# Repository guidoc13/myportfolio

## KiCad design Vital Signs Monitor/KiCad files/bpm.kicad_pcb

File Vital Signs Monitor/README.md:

# Data Logger de Signos Vitales (LPC845 + ESP32)

## Descripción General
Este proyecto consiste en el desarrollo de un sistema embebido para la adquisición, registro y monitoreo de señales biomédicas. El sistema utiliza un microcontrolador **ARM Cortex-M0+ (LPC845)** para el procesamiento de señales y un módulo **ESP** para la transmisión de datos, integrando lógicas de 3.3V y protecciones de hardware.

## Especificaciones Técnicas y Criterios de Diseño
Para garantizar la integridad de las señales analógicas y la estabilidad del sistema, se aplicaron los siguientes criterios durante el diseño en **KiCad**:

* **Integridad de Señal:** Implementación de capacitores de desacople de 100nF en los pines de alimentación de cada dispositivo para filtrar ruido de alta frecuencia.
* **Gestión de Retornos:** Diseño de un plano de masa (*GND Pour*) continuo en la capa superior (*Top Layer*) para blindaje electromagnético y minimización de corrientes de retorno.
* **Compatibilidad de Lógica:** Manejo de niveles lógicos de 3.3V y diseño de protecciones de hardware para preservar la integridad de los microcontroladores.

## Documentación y Fabricación
* **Paquete Gerber:** Generación de archivos vectoriales para la fabricación de la placa (Cobre, Máscara y Serigrafía).
* **Bill of Materials (BOM):** Lista de materiales detalladas para los componentes.
* **Composición 3D:** Modelado y visualización final de la placa mediante archivos .step.

## Vistas del Proyecto

## Ruteo de Capas (Top & Bottom)

---

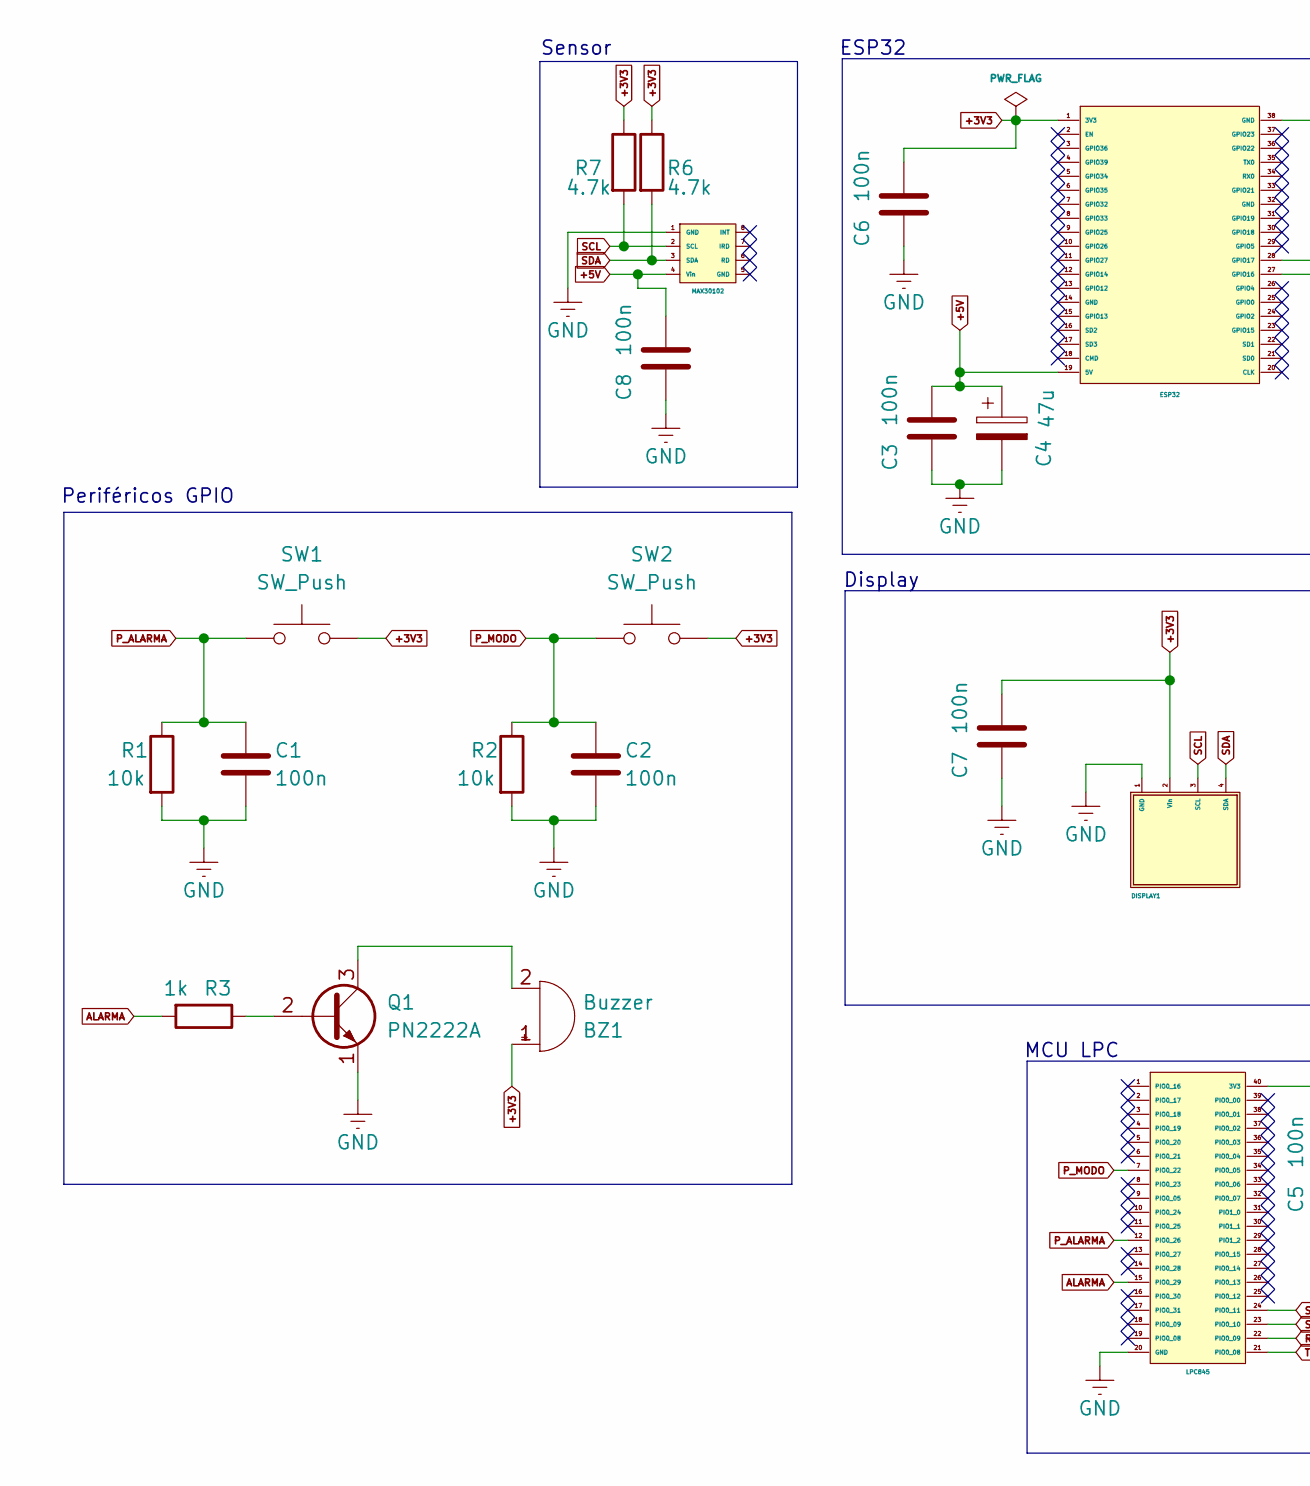
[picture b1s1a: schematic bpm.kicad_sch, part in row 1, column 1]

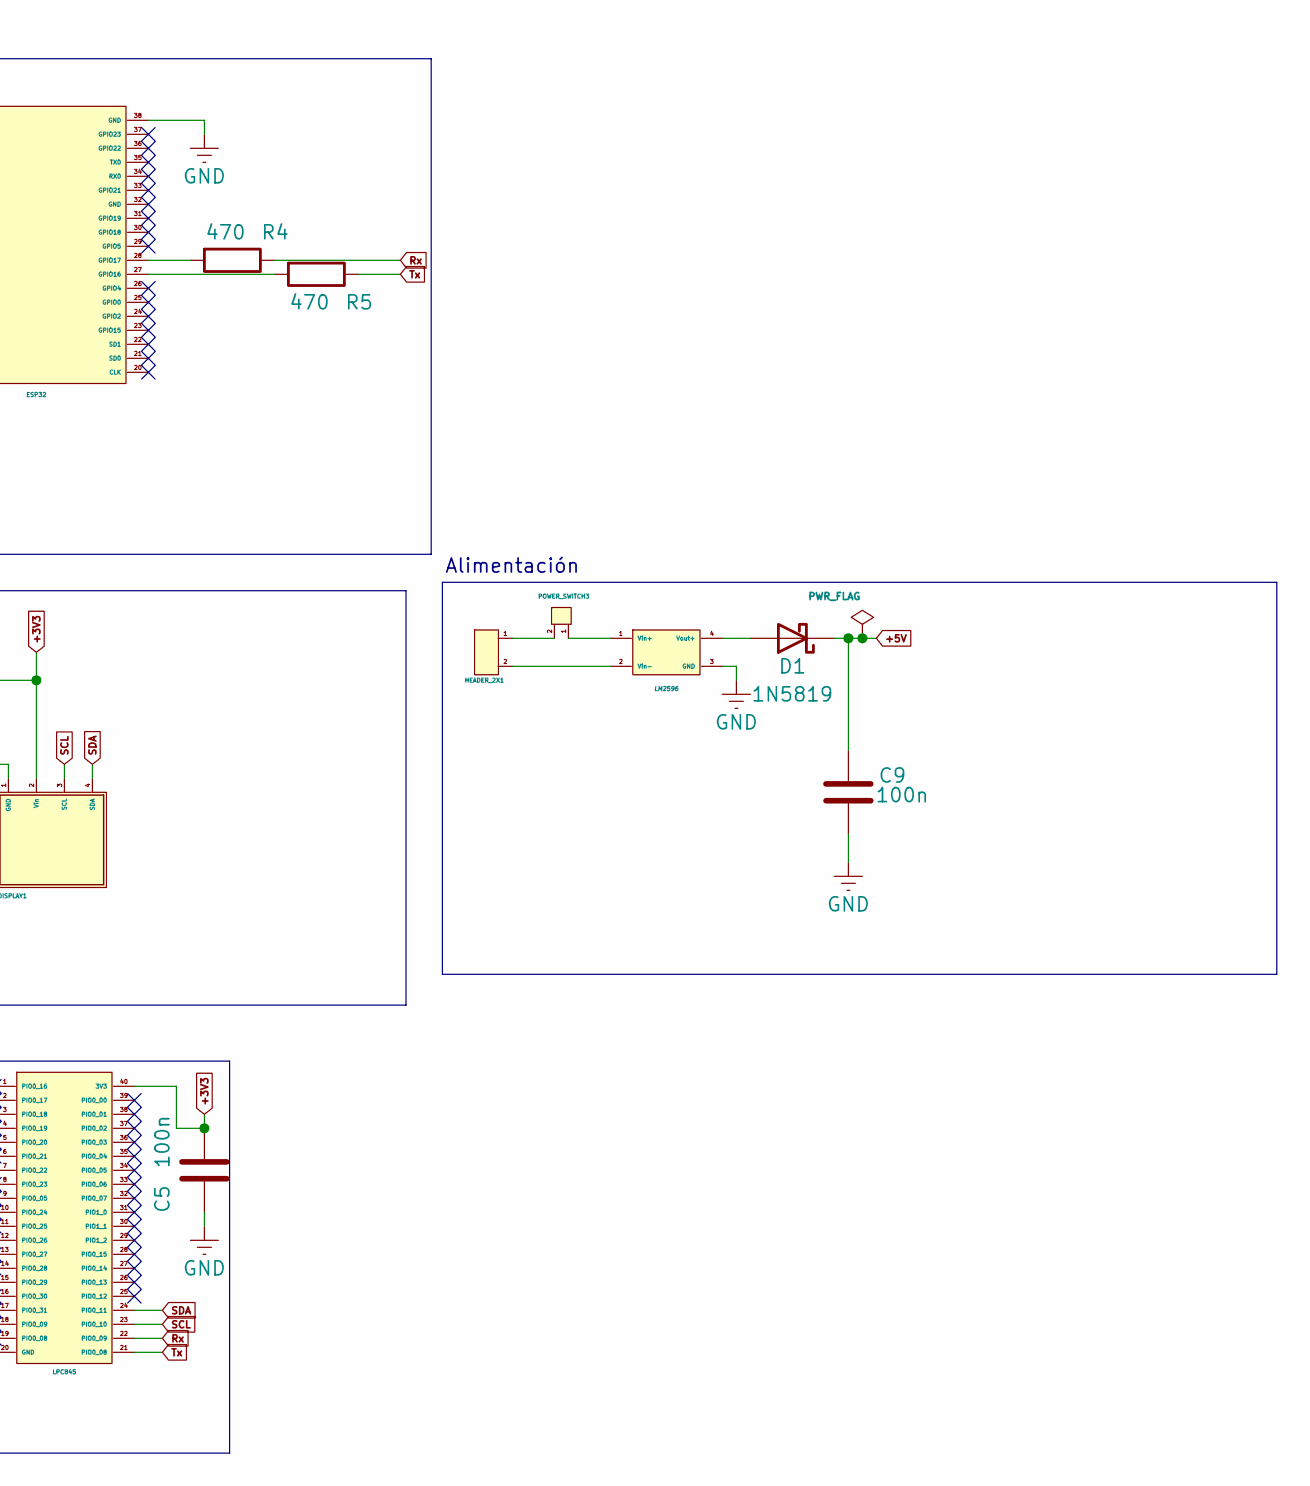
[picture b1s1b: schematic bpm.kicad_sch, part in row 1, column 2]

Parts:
BZ1: Buzzer; Buzzer_12x9.5RM7.6
C1, C2, C3, C5, C6, C7, C8, C9: 100n; C_Disc_D4.3mm_W1.9mm_P5.00mm
C4: 47u; CP_Radial_D5.0mm_P2.50mm
D1: 1N5819; D_DO-41_SOD81_P10.16mm_Horizontal
DISPLAY1: DISPLAY_128X64
ESP32: ESP32_MODULE
HEADER_2X1: TerminalBlock_MaiXu_MX126-5.0-02P_1x02_P5.00mm
LM2596: LM2596_MODULE
LPC845: LPC845_MODULE
MAX30102: MAX30102
POWER_SWITCH3: SW_CK_JS202011CQN_DPDT_Straight
Q1: PN2222A; TO-92_Inline
R1, R2: 10k; R_Axial_DIN0207_L6.3mm_D2.5mm_P10.16mm_Horizontal
R3: 1k; R_Axial_DIN0207_L6.3mm_D2.5mm_P10.16mm_Horizontal
R4, R5: 470; R_Axial_DIN0207_L6.3mm_D2.5mm_P10.16mm_Horizontal
R6, R7: 4.7k; R_Axial_DIN0207_L6.3mm_D2.5mm_P10.16mm_Horizontal
SW1, SW2: SW_Push; SW_PUSH_6mm

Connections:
+3V3: BZ1.1 (+), C5.2, C6.2, C7.2, DISPLAY1.2 (Vin), ESP32.1 (3V3), LPC845.40 (3V3), R6.1, R7.1, SW1.2, SW2.2
+5V: C3.2, C4.1, C8.2, C9.2, D1.1 (K), ESP32.19 (5V), MAX30102.4 (Vin)
ALARMA: LPC845.15 (PIO0_29), R3.2
GND: C1.2, C2.2, C3.1, C4.2, C5.1, C6.1, C7.1, C8.1, C9.1, DISPLAY1.1 (GND), ESP32.38 (GND), LM2596.3 (GND), LPC845.20 (GND), MAX30102.1 (GND), Q1.1 (E), R1.2, R2.2
unnamed: BZ1.2 (-), Q1.3 (C)
unnamed: D1.2 (A), LM2596.4 (Vout+)
unnamed: ESP32.27 (GPIO16), R5.2
unnamed: ESP32.28 (GPIO17), R4.2
unnamed: HEADER_2X1.1, POWER_SWITCH3.2
unnamed: LM2596.1 (Vin+), POWER_SWITCH3.1
unnamed: HEADER_2X1.2, LM2596.2 (Vin-)
unnamed: Q1.2 (B), R3.1
P_ALARMA: C1.1, LPC845.12 (PIO0_26), R1.1, SW1.1
P_MODO: C2.1, LPC845.7 (PIO0_22), R2.1, SW2.1
Rx: LPC845.22 (PIO0_09), R4.1
SCL: DISPLAY1.3 (SCL), LPC845.23 (PIO0_10), MAX30102.2 (SCL), R7.2
SDA: DISPLAY1.4 (SDA), LPC845.24 (PIO0_11), MAX30102.3 (SDA), R6.2
Tx: LPC845.21 (PIO0_08), R5.1

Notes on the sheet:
ESP32
Display
MCU LPC
Alimentación
Sensor
Periféricos GPIO

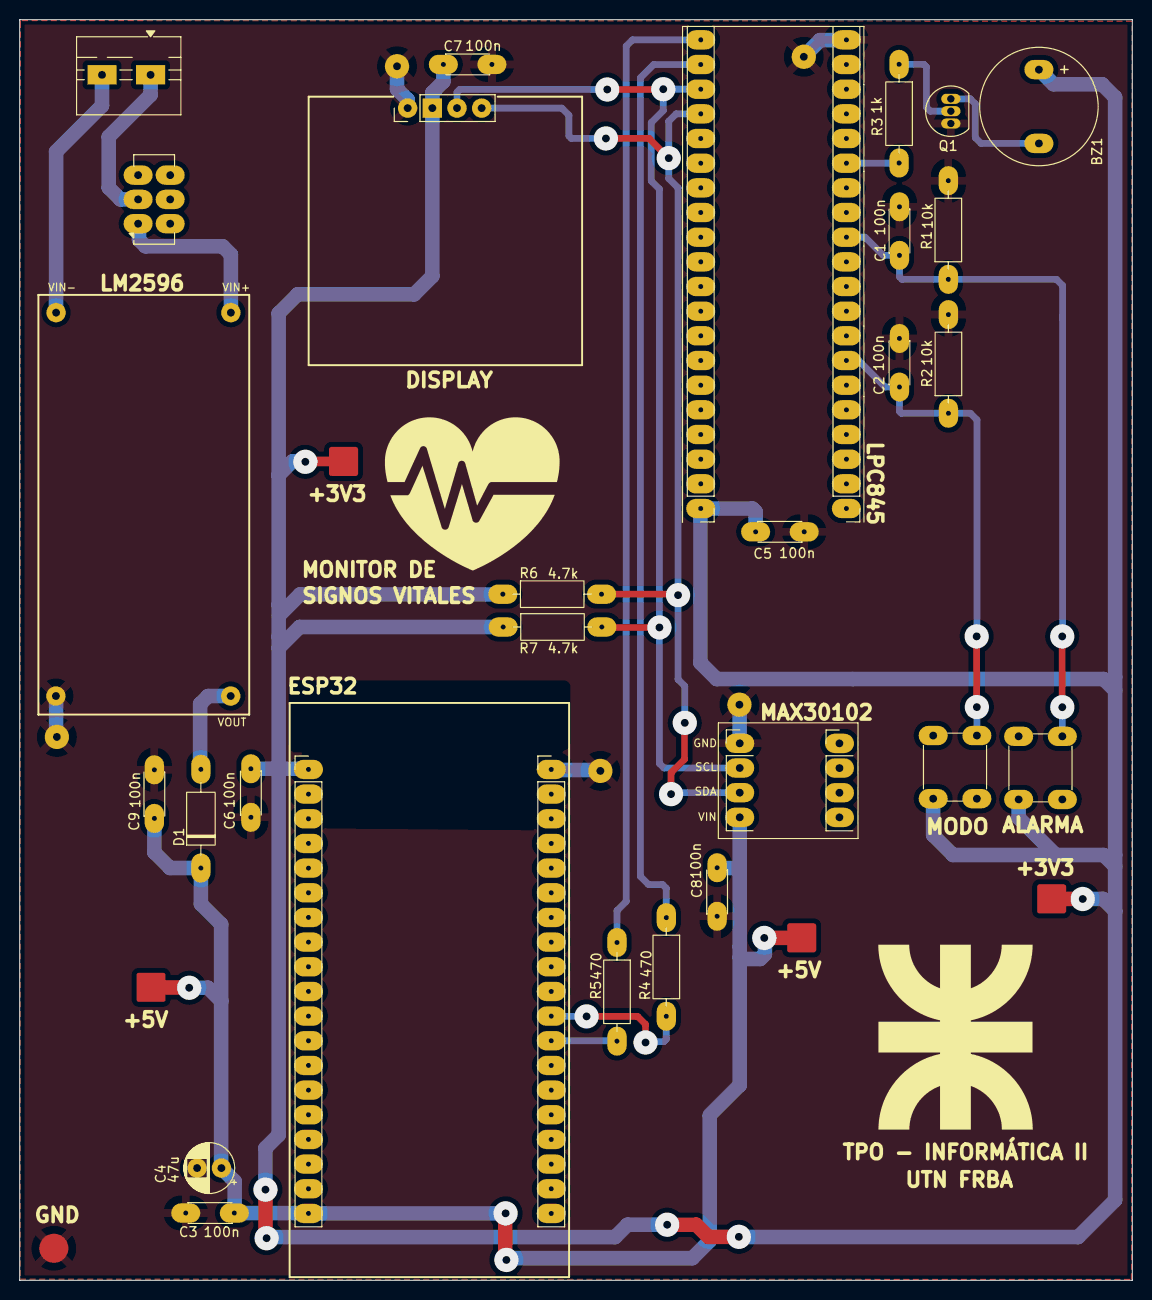
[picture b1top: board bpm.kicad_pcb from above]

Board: 2 copper layers, 114.6 x 129.8 mm, 28 parts (0 on the bottom side), 18 nets.

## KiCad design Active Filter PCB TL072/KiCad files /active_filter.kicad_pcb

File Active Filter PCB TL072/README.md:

# Diseño de PCB: Filtro Analógico Activo (Low Pass & Notch) con TL072
Este proyecto consiste en el diseño y ruteo de una PCB para un Filtro Analógico Activo del tipo Pasa Bajos y Notch utilizando el Amplificador Operacional TL072. El objetivo principal fue realizar el análisis de respuesta en frecuencia empleando un Analizador de Redes.    

## Vistas del Proyecto

## Criterios de Diseño Aplicados

Durante el ruteo de la placa, los criterios de diseño que se tomaron para garantizar la estabilidad del circuito fueron:

* **Desacople de Alimentación Vcc:** Ubicación de capacitores cerámicos de 100nF en los pines de +Vcc y -Vcc para mitigar los efectos del ruido de alta frecuencia en la entrada de la alimentación del Op. Amp.
* **Plano GND en la Top Layer:** Implementación de un plano de masa continuo (*GND Pour*) en la capa Top para blindar el circuito y reducir significativamente las corrientes de retorno.

## Ruteo de Capas (Top & Bottom)

## Respuesta en frecuencia de cada filtro

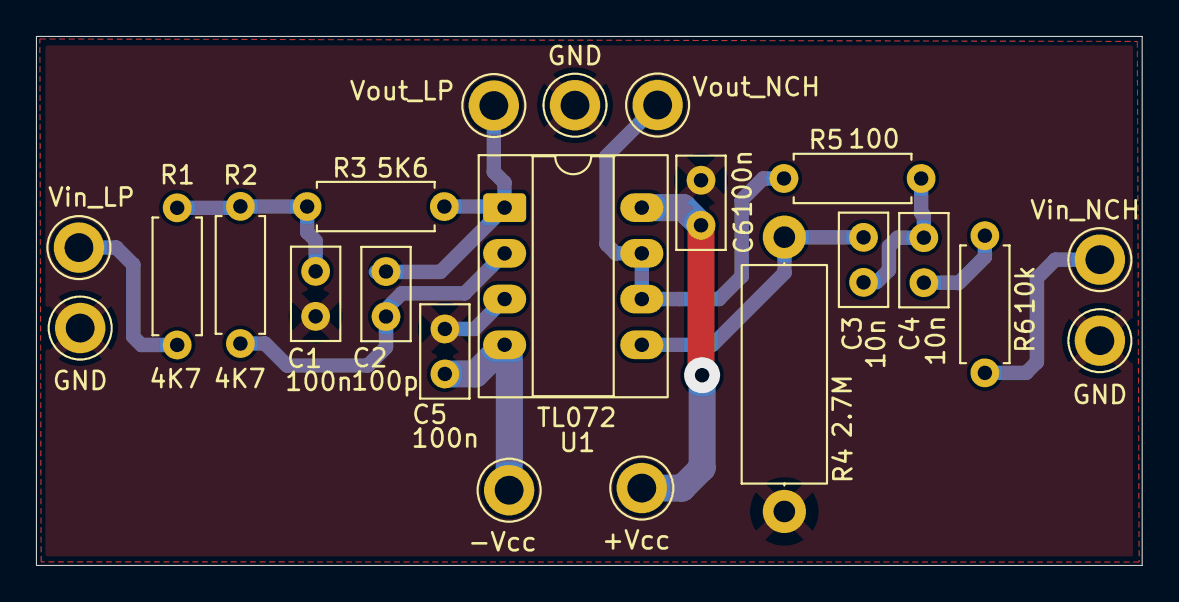
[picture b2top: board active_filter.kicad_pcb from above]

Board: 2 copper layers, 61.4 x 29.4 mm, 22 parts (0 on the bottom side), 12 nets.

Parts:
+Vcc: +Vcc_TP; TestPoint_Keystone_5005-5009_Compact
-Vcc: -Vcc_TP; TestPoint_Keystone_5005-5009_Compact
C1, C5, C6: 100n; C_Disc_D5.0mm_W2.5mm_P2.50mm
C2: 100p; C_Disc_D5.0mm_W2.5mm_P2.50mm
C3, C4: 10n; C_Disc_D5.0mm_W2.5mm_P2.50mm
GND: GND_Vout_LP; TestPoint_Keystone_5005-5009_Compact
GND#2: GND_Vin_NOTCH; TestPoint_Keystone_5005-5009_Compact
GND#3: GND_Vin_LP; TestPoint_Keystone_5005-5009_Compact
R1, R2: 4K7; R_Axial_DIN0207_L6.3mm_D2.5mm_P7.62mm_Horizontal
R3: 5K6; R_Axial_DIN0207_L6.3mm_D2.5mm_P7.62mm_Horizontal
R4: 2.7M; R_Axial_DIN0414_L11.9mm_D4.5mm_P15.24mm_Horizontal
R5: 100; R_Axial_DIN0207_L6.3mm_D2.5mm_P7.62mm_Horizontal
R6: 10k; R_Axial_DIN0207_L6.3mm_D2.5mm_P7.62mm_Horizontal
U1: TL072; CERDIP-8_W7.62mm_SideBrazed_LongPads_Socket
Vin_LP: Vin_LOW_PASS; TestPoint_Keystone_5005-5009_Compact
Vin_NCH: Vin_NOTCH; TestPoint_Keystone_5005-5009_Compact
Vout_LP: Vout_LOW_PASS; TestPoint_Keystone_5005-5009_Compact
Vout_NCH: Vout_Notch; TestPoint_Keystone_5005-5009_Compact

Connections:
+Vcc: +Vcc.1, C6.1, U1.8 (V+)
-Vcc: -Vcc.1, C5.1, U1.4 (V-)
GND: C1.2, C5.2, C6.2, GND.1, GND#2.1, GND#3.1, R4.1
unnamed: C1.1, R1.2, R2.1, R3.1
unnamed: C2.2, R3.2, U1.1, Vout_LP.1
unnamed: C3.1, C4.2, R5.1
unnamed: C4.1, R6.2
unnamed: R1.1, Vin_LP.1
unnamed: R6.1, Vin_NCH.1
unnamed: C2.1, R2.2, U1.2 (-)
unnamed: C3.2, R4.2, U1.5 (+)
unnamed: R5.2, U1.6 (-), U1.7, Vout_NCH.1

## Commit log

2026-03-13 Filtro activo TL072
2026-03-13 Active Filter TL072
2026-03-17 Vital Signs Monitor
